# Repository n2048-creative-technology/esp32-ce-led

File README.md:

# ESP32-C6 LED Controller Board

A compact 2-layer PCB built around the **ESP32-C6-WROOM-1** module, providing
USB-C power/programming, on-board 3.3V regulation, ESD-protected USB
data lines, a reset button, and an addressable/status LED header. All
electronic parts are sourced against JLCPCB's live parts catalog for
turnkey assembly.

## 3D Renders

| Top side (regulator / passives) | Bottom side (ESP32 module / USB-C) |
|---|---|
|  |  |

## Schematic

Full-resolution vector version: [`docs/images/schematic.pdf`](docs/images/schematic.pdf)

## PCB Layout

*Copper (F.Cu / B.Cu), silkscreen, and solder mask layers, board outline shown.*

## Board Specs

- **Size:** 20.55 mm × 35.55 mm
- **Layers:** 2 (F.Cu / B.Cu)
- **MCU:** ESP32-C6-WROOM-1-N8 (Wi-Fi 6, Bluetooth 5 LE, Zigbee/Thread 802.15.4, 8 MB flash)
- **Power in:** USB-C (5V), on-board AMS1117-3.3 LDO regulator for 3.3V rail
- **USB protection:** USBLC6-2SC6-FS ESD protection on D+/D-
- **User I/O:** Reset button (SW1), status LED (D1), 2× 3-pin headers (J1/J2) for external LED/peripheral connections
- **ESD protection:** ESD9B3.3ST5G on EN line

## Bill of Materials

All parts verified against the live JLCPCB Open Platform API (real-time stock/pricing).
Full machine-readable BOM: [`BOM_jlcpcb_verified.csv`](BOM_jlcpcb_verified.csv)

| Ref | Part | LCSC # | Library |
|---|---|---|---|
| U1 | ESP32-C6-WROOM-1-N8 | C5366877 | Extended |
| U2 | USBLC6-2SC6-FS | C6807798 | Extended |
| U3 | AMS1117-3.3(TO-252) | C41347676 | Extended |
| D1 | KT-0603R (red LED) | C2286 | **Basic** |
| D4 | ESD9B3.3ST5G | C96512 | Extended |
| SW1 | B3U-1000P (tactile switch) | C231329 | Extended |
| J1, J2 | HX PH254-01-03-Z-L11.5 (1×3 header) | C52016391 | Extended |
| J4 | USB4105-GF-A (USB-C receptacle, 16P) | C3020560 | Extended |
| R1, R2 | 5.1kΩ 0402 | C25905 | **Basic** |
| R3 | 1kΩ 0402 | C11702 | **Basic** |
| R7, R8 | 10kΩ 0402 | C25744 | **Basic** |
| C1, C6 | 100nF 01005 | C307376 | Extended |
| C2, C3 | 22µF 0805 | C129302 | Extended |
| C4 | 1µF 0603 | C15849 | **Basic** |
| C5 | 10µF 0603 | C7472959 | Extended |

## Manufacturing

Board is set up for JLCPCB fabrication + assembly out of the box.
`production/` contains regenerated, verified fabrication files:

- `esp32-c3-led_gerbers.zip` — Gerbers + Excellon drill file (upload
  directly to JLCPCB's PCB order)
- `bom.csv` — JLCPCB-format BOM with a populated `LCSC Part #` column
  for every line (Comment / Designator / Footprint / LCSC Part #);
  each part number is a live, in-stock JLCPCB catalog match
- `positions.csv` — CPL / pick-and-place file (Ref, Val, Package,
  PosX, PosY, Rot, Side), regenerated from the current board so
  bottom-side parts (J1, J2, J4, U1) are correctly marked `bottom`

`esp32-c3-led.kicad_pro` / `.kicad_sch` / `.kicad_pcb` remain the
authoritative KiCad 9 source files; every part also carries `LCSC` and
`MPN` custom fields on its schematic symbol.

> **Note:** an earlier BOM/CPL pair generated by the Fabrication
> Toolkit KiCad plugin shipped with an empty `LCSC Part #` column,
> which caused JLCPCB's auto-matcher to select wrong/out-of-stock
> substitutes and fail to match the connectors (J1/J2/J4) entirely.
> The files above were regenerated directly from the schematic's
> verified LCSC data and confirmed against the live JLCPCB API —
> use these instead of re-running the plugin unless the design changes.

### Design Rule Check status

Verified clean via `kicad-cli pcb drc`: only 3 benign warnings remain
(`lib_footprint_mismatch` on C1/C6/D1, confirming intentional local
customizations — see below). No copper clearance errors, no
dangling/floating silkscreen text, no component placement changes.

### Assembly orientation / silkscreen clarity

To avoid JLCPCB assembly clarification requests, every part with a
genuine orientation dependency has an unambiguous silkscreen or
Gerber-encoded marker:

- **D1 (LED, polarized)** — cathode (pin 1) marked with a bold bar on
  the silkscreen outline, matching its datasheet K/A pinout.
- **SW1, U2** — tactile switch and ESD IC footprints already carry a
  pin-1 triangle marker from their library footprints.
- **J1, J2 (headers)** — pin 1 uses a square pad vs. round pads on 2/3,
  the standard machine-readable convention (read directly from the
  Gerbers/CPL, not silkscreen).
- **J4 (USB-C receptacle), U3 (TO-252 regulator)** — mechanically keyed
  / self-orienting packages; cannot be placed backwards.
- **D4 (ESD9B3.3ST5G)** — confirmed **bidirectional** TVS diode per
  datasheet; orientation is electrically irrelevant, so intentionally
  left unmarked.
- **U1 (ESP32-C6-WROOM-1)** — uses Espressif's official reference
  footprint; JLCPCB sources rotation from the CPL file, not visual
  silkscreen inspection, for this standard module.

## Repo Layout

```
esp32-c3-led.kicad_pro      KiCad project
esp32-c3-led.kicad_sch      Schematic
esp32-c3-led.kicad_pcb      PCB layout
BOM_jlcpcb_verified.csv     Reference BOM with LCSC part numbers (grouped by value)
docs/images/                Renders and diagrams (this README)
production/                  JLCPCB-ready fabrication output:
  esp32-c3-led_gerbers.zip     Gerbers + drill (upload as-is)
  bom.csv                      JLCPCB BOM (Comment/Designator/Footprint/LCSC Part #)
  positions.csv                CPL / pick-and-place file
  gerbers/                     Individual Gerber/drill layer files
```

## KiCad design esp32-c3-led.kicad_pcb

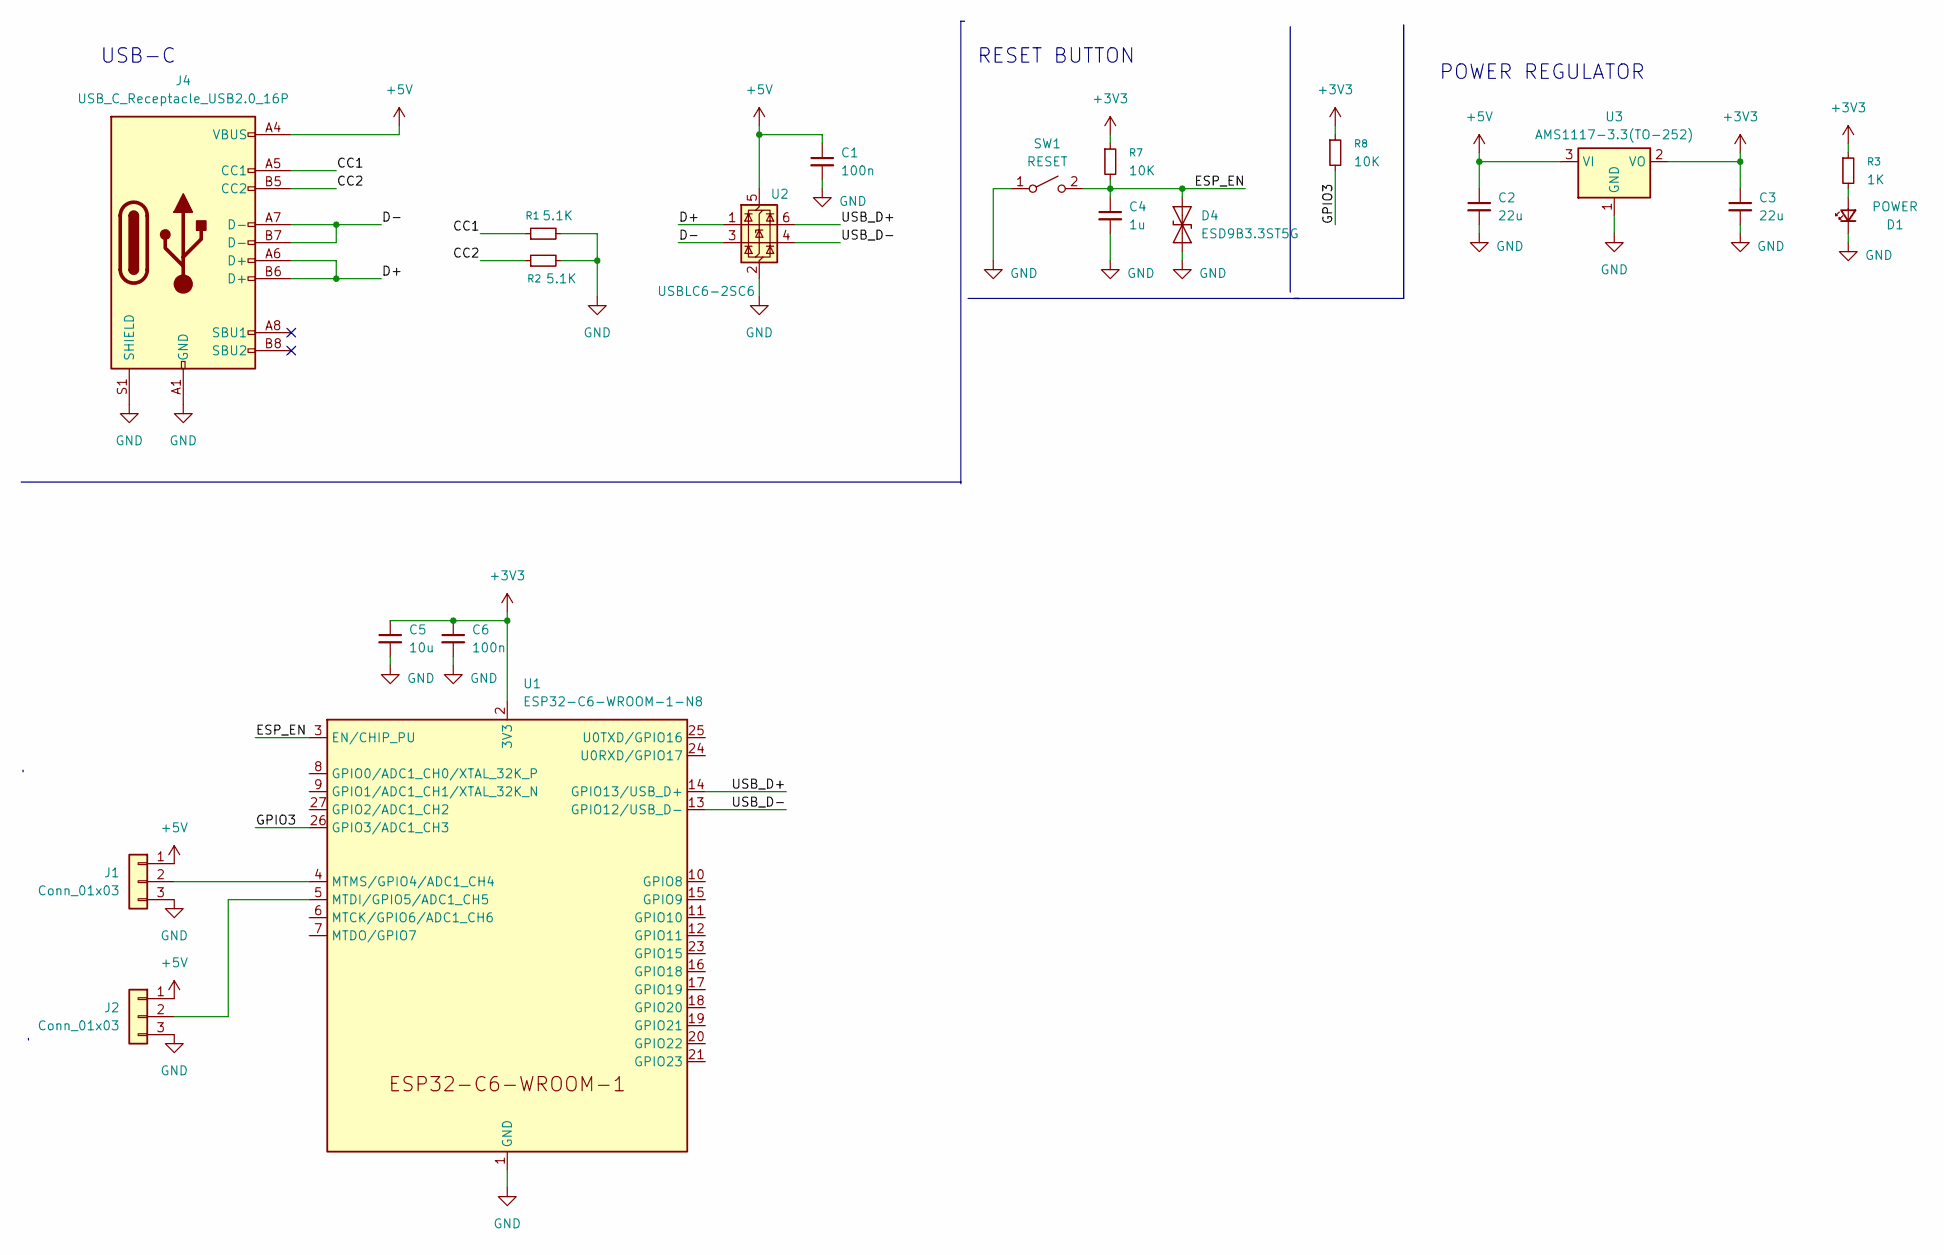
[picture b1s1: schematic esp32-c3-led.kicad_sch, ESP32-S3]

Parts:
C1, C6: 100n; C_01005_0402Metric; MPN CL02A104MQ2NNNC; LCSC C307376
C2, C3: 22u; C_0805_2012Metric; MPN 0805X226M160NT; LCSC C129302
C4: 1u; C_0603_1608Metric; MPN CL10A105KB8NNNC; LCSC C15849
C5: 10u; C_0603_1608Metric; MPN HGC0603R5106M160NTHJ; LCSC C7472959
D1: POWER; LED_0603_1608Metric; MPN KT-0603R; LCSC C2286
D4: ESD9B3.3ST5G; D_SOD-923; MPN ESD9B3.3ST5G; LCSC C96512
J1, J2: Conn_01x03; PinHeader_1x03_P2.54mm_Vertical; MPN HX PH254-01-03-Z-L11.5; LCSC C52016391
J4: USB_C_Receptacle_USB2.0_16P; USB_C_Receptacle_GCT_USB4105-xx-A_16P_TopMnt_Horizontal; MPN USB4105-GF-A; LCSC C3020560
R1, R2: 5.1K; R_0402_1005Metric_Pad0.72x0.64mm_HandSolder; MPN 0402WGF5101TCE; LCSC C25905
R3: 1K; R_0402_1005Metric_Pad0.72x0.64mm_HandSolder; MPN 0402WGF1001TCE; LCSC C11702
R7, R8: 10K; R_0402_1005Metric_Pad0.72x0.64mm_HandSolder; MPN 0402WGF1002TCE; LCSC C25744
SW1: RESET; SW_SPST_B3U-1000P; MPN B3U-1000P; LCSC C231329
U1: ESP32-C6-WROOM-1-N8; ESP32-C6-WROOM-1; MPN ESP32-C6-WROOM-1-N8; LCSC C5366877
U2: USBLC6-2SC6; SOT-23-6; MPN USBLC6-2SC6-FS; LCSC C6807798
U3: AMS1117-3.3(TO-252); TO-252-3_TabPin2; MPN AMS1117-3.3(TO-252); LCSC C41347676

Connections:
+3V3: C3.1, C5.1, C6.1, R3.1, R7.1, R8.1, U1.2 (3V3), U3.2 (VO)
+5V: C1.1, C2.1, J1.1, J2.1, J4.A4 (VBUS), J4.A9 (VBUS), J4.B4 (VBUS), J4.B9 (VBUS), U2.5 (VBUS), U3.3 (VI)
CC1: J4.A5 (CC1), R1.1
CC2: J4.B5 (CC2), R2.1
D+: J4.A6 (D+), J4.B6 (D+), U2.1 (I/O1)
D-: J4.A7 (D-), J4.B7 (D-), U2.3 (I/O2)
ESP_EN: C4.1, D4.2 (A2), R7.2, SW1.2 (B), U1.3 (EN/CHIP_PU)
GND: C1.2, C2.2, C3.2, C4.2, C5.2, C6.2, D1.1 (K), D4.1 (A1), J1.3, J2.3, J4.A1 (GND), J4.A12 (GND), J4.B1 (GND), J4.B12 (GND), J4.S1 (SHIELD), R1.2, R2.2, SW1.1 (A), U1.1 (GND), U1.28 (GND), U1.29 (GND), U2.2 (GND), U3.1 (GND)
GPIO3: R8.2, U1.26 (GPIO3/ADC1_CH3)
unnamed: D1.2 (A), R3.2
unnamed: J1.2, U1.4 (MTMS/GPIO4/ADC1_CH4)
unnamed: J2.2, U1.5 (MTDI/GPIO5/ADC1_CH5)
USB_D+: U1.14 (GPIO13/USB_D+), U2.6 (I/O1)
USB_D-: U1.13 (GPIO12/USB_D-), U2.4 (I/O2)

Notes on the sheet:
RESET BUTTON
USB-C
POWER REGULATOR

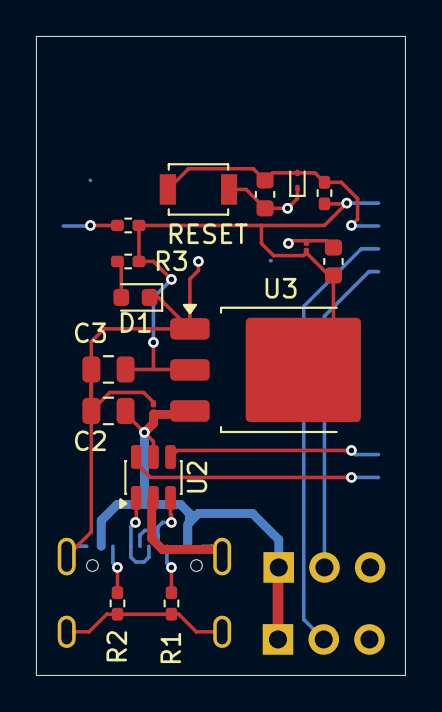
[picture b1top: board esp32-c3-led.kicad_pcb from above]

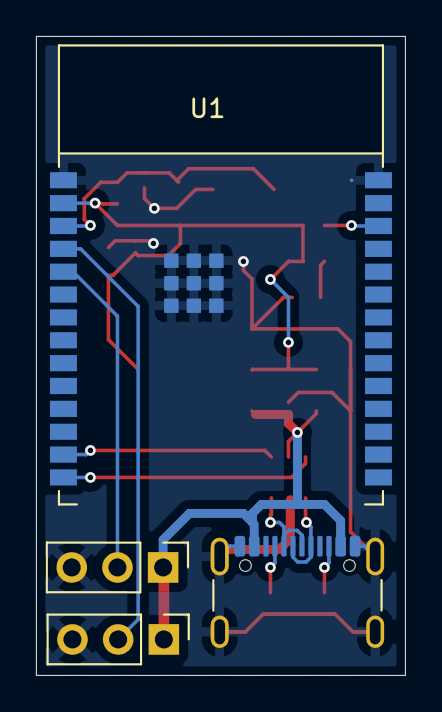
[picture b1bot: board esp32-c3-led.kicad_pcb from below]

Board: 2 copper layers, 20.5 x 35.5 mm, 20 parts (4 on the bottom side), 14 nets.

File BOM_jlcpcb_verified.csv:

reference,value,footprint,layer
U3,LM1117DT-3.3,Package_TO_SOT_SMD:TO-252-3_TabPin2,F.Cu
C5,10u,Capacitor_SMD:C_0603_1608Metric,F.Cu
D4,ESD3.3,Diode_SMD:D_SOD-923,F.Cu
C2,22u,Capacitor_SMD:C_0805_2012Metric,F.Cu
C1,100n,Capacitor_SMD:C_01005_0402Metric_Pad0.57x0.30mm_HandSolder,F.Cu
C4,1u,Capacitor_SMD:C_0603_1608Metric,F.Cu
D1,POWER,LED_SMD:LED_0603_1608Metric,F.Cu
U2,USBLC6-2SC6,Package_TO_SOT_SMD:SOT-23-6,F.Cu
R7,10K,Resistor_SMD:R_0402_1005Metric_Pad0.72x0.64mm_HandSolder,F.Cu
SW1,RESET,Button_Switch_SMD:SW_SPST_B3U-1000P,F.Cu
R2,5.1K,Resistor_SMD:R_0402_1005Metric_Pad0.72x0.64mm_HandSolder,F.Cu
R1,5.1K,Resistor_SMD:R_0402_1005Metric_Pad0.72x0.64mm_HandSolder,F.Cu
C6,100n,Capacitor_SMD:C_01005_0402Metric_Pad0.57x0.30mm_HandSolder,F.Cu
R3,1K,Resistor_SMD:R_0402_1005Metric_Pad0.72x0.64mm_HandSolder,F.Cu
R8,10K,Resistor_SMD:R_0402_1005Metric_Pad0.72x0.64mm_HandSolder,F.Cu
C3,22u,Capacitor_SMD:C_0805_2012Metric,F.Cu
J1,Conn_01x03,Connector_PinHeader_2.54mm:PinHeader_1x03_P2.54mm_Vertical,B.Cu
J4,USB_C_Receptacle_USB2.0_16P,Connector_USB:USB_C_Receptacle_GCT_USB4105-xx-A_16P_TopMnt_Horizontal,B.Cu
U1,ESP32-C6-WROOM-1,PCM_Espressif:ESP32-C6-WROOM-1,B.Cu
J2,Conn_01x03,Connector_PinHeader_2.54mm:PinHeader_1x03_P2.54mm_Vertical,B.Cu
